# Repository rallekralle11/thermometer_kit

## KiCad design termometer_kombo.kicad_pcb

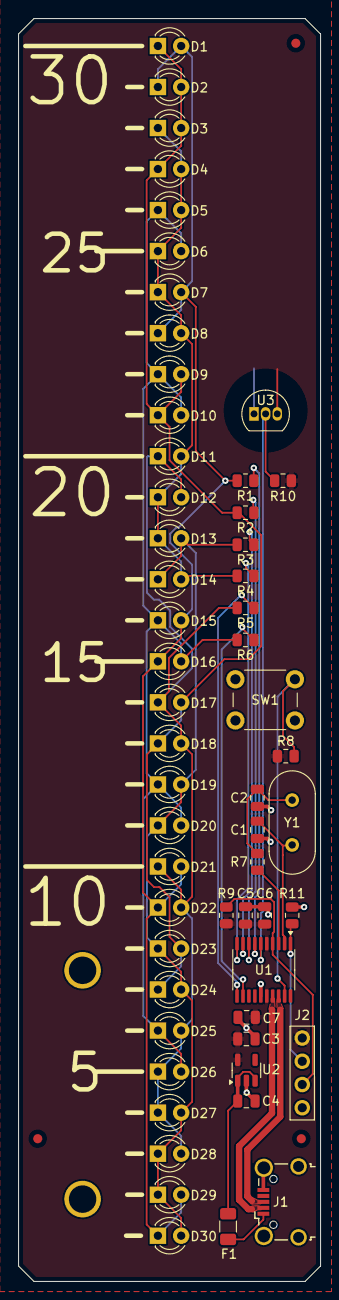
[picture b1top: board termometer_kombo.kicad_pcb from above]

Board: 2 copper layers, 33.0 x 138.0 mm, 61 parts (0 on the bottom side), 25 nets.

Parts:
C1, C2: TBD; C_0805_2012Metric
C3, C4, C5: 1µF; C_0805_2012Metric
C6, C7: 100nF; C_0805_2012Metric
D1, D2, D3, D4, D5, D6, D7, D8, D9, D10, D11, D12, D13, D14, D15, D16, D17, D18, D19, D20, D21, D22, D23, D24, D25, D26, D27, D28, D29, D30: LED; LED_D3.0mm
F1: Fuse_Small; Fuse_1206_3216Metric
FID1, FID1#2, FID1#3: Fiducial_1mm_Mask2mm
J1: USB_B_Micro; USB_Micro-B_Wuerth_629105150521_CircularHoles
J2: Conn_01x04; PinHeader_1x04_P2.54mm_Vertical
R1, R2, R3, R4, R5, R6: 22; R_0805_2012Metric
R7: TBD; R_0805_2012Metric
R8, R9, R10, R11: 5K; R_0805_2012Metric
REF2, REF2#2: Mounting_Wuerth_WA-SMSI-M1.6_H2.5mm_ThreadDepth1.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; Mounting_Wuerth_WA-SMSI-M1.6_H2.5mm_ThreadDepth1.5mm_NoNPTH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
SW1: SW_MEC; SW_PUSH_6mm
U1: STM32F070F6Px; TSSOP-20_4.4x6.5mm_P0.65mm
U2: RT9080; SOT-23-5
U3: DS18B20; TO-92_Inline
Y1: TBD; Crystal_HC18-U_Vertical

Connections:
+3.3V: C3.2, C5.1, C6.1, C7.1, J2.1, R8.1, R9.2, R10.1, U1.5 (VDDA), U1.16 (VDD), U2.5 (OUT), U3.3 (V_{DD})
+5V: C4.2, F1.2, U2.1 (IN), U2.3 (EN)
B: J2.2, R11.2, U1.1 (BOOT0)
D+: J1.3 (D+), U1.18 (PA10/PA12)
D-: J1.2 (D-), U1.17 (PA9/PA11)
GND: C1.1, C2.1, C3.1, C4.1, C5.2, C6.2, C7.2, J1.5 (GND), J1.6 (Shield), J2.4, R11.1, SW1.1 (A), U1.15 (VSS), U2.2 (GND), U3.1 (GND)
IO0: R10.2, U1.6 (PA0), U3.2 (DQ)
IO1: R1.1, U1.7 (PA1)
IO2: R2.1, U1.8 (PA2)
IO3: R3.1, U1.9 (PA3)
IO4: R4.1, U1.10 (PA4)
IO5: R5.1, U1.11 (PA5)
IO6: R6.1, U1.12 (PA6)
IO13: R8.2, SW1.3 (B), U1.19 (PA13)
unnamed: C2.2, R7.1, Y1.1
unnamed: D1.2 (A), D2.1 (K), D7.2 (A), D8.1 (K), D15.2 (A), D16.1 (K), D21.2 (A), D22.1 (K), D29.2 (A), D30.1 (K), R1.2
unnamed: D1.1 (K), D2.2 (A), D3.2 (A), D4.1 (K), D9.2 (A), D10.1 (K), D17.2 (A), D18.1 (K), D23.2 (A), D24.1 (K), R2.2
unnamed: D5.1 (K), D6.2 (A), D9.1 (K), D10.2 (A), D15.1 (K), D16.2 (A), D19.1 (K), D20.2 (A), D25.1 (K), D26.2 (A), R6.2
unnamed: D3.1 (K), D4.2 (A), D5.2 (A), D6.1 (K), D7.1 (K), D8.2 (A), D11.2 (A), D12.1 (K), D13.1 (K), D14.2 (A), R4.2
unnamed: D11.1 (K), D12.2 (A), D17.1 (K), D18.2 (A), D21.1 (K), D22.2 (A), D25.2 (A), D26.1 (K), D27.1 (K), D28.2 (A), R5.2
unnamed: D13.2 (A), D14.1 (K), D19.2 (A), D20.1 (K), D23.1 (K), D24.2 (A), D27.2 (A), D28.1 (K), D29.1 (K), D30.2 (A), R3.2
unnamed: F1.1, J1.1 (VBUS)
unnamed: C1.2, U1.2 (PF0), Y1.2
unnamed: R7.2, U1.3 (PF1)
RST: J2.3, R9.1, U1.4 (NRST)

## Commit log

2024-12-28 init
